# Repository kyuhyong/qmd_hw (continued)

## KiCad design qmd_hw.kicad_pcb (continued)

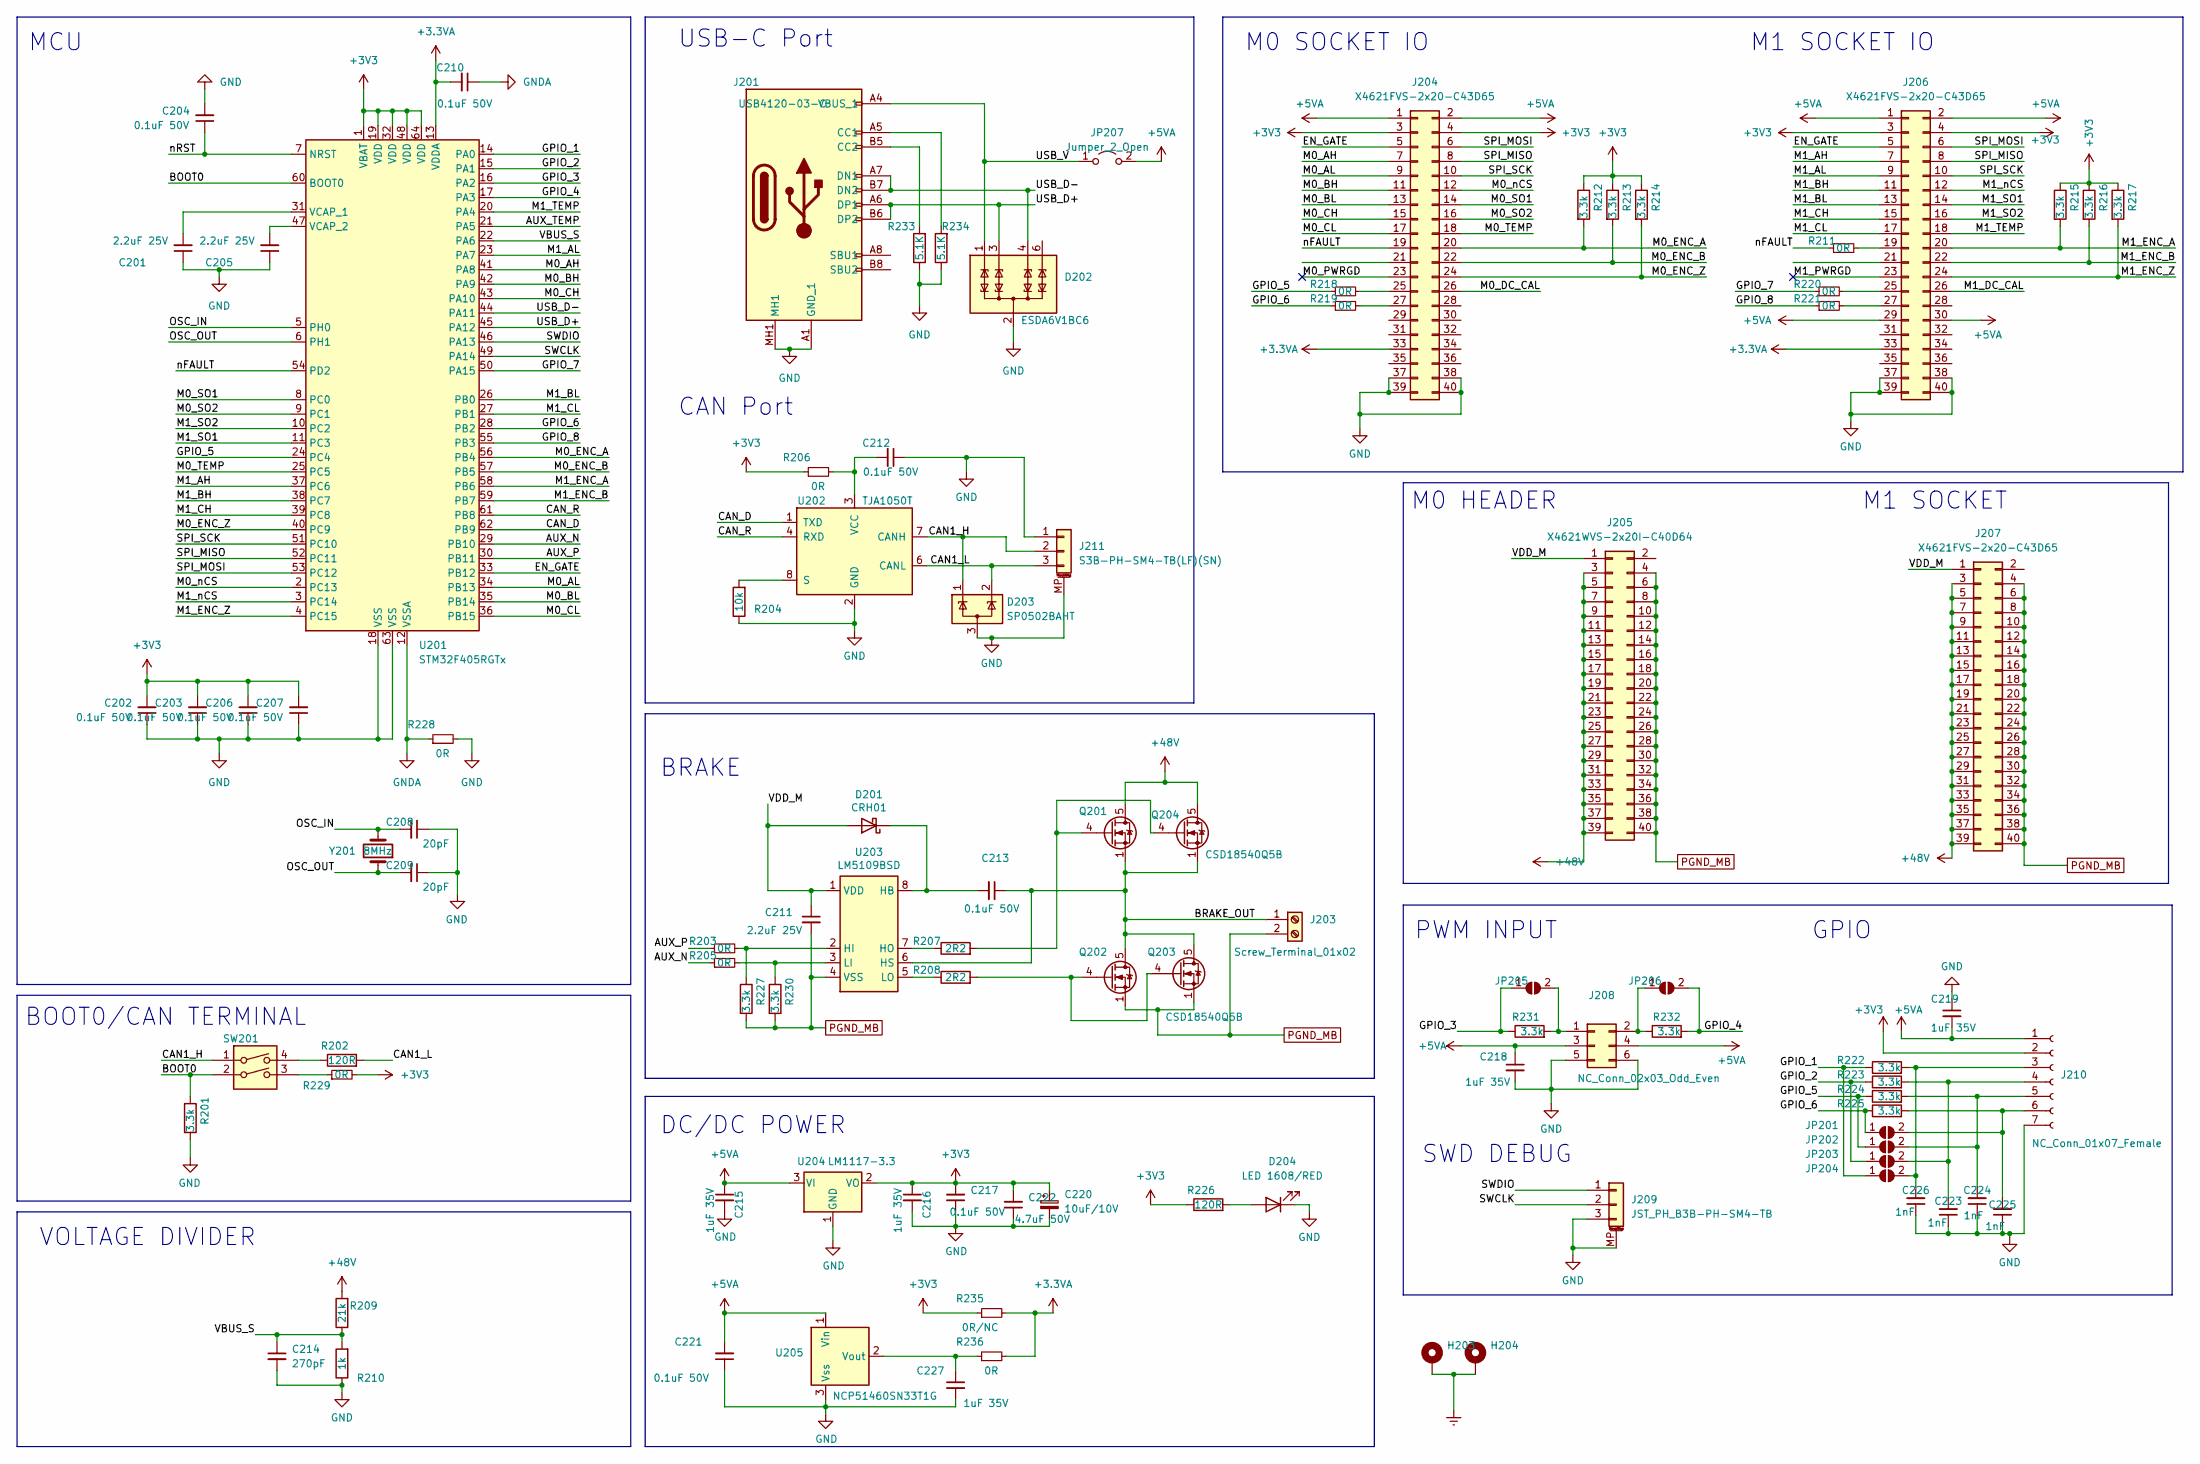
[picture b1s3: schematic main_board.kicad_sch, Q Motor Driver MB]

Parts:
C201, C205, C211: 2.2uF 25V; C_0603_1608Metric; MPN CL10A225KB8NNNC; JLCPN C913904
C202, C203, C204, C206, C207, C210, C212, C213, C217, C221: 0.1uF 50V; C_0603_1608Metric; MPN CL10B104KB8NNNC; JLCPN C1591
C208, C209: 20pF; C_0603_1608Metric; MPN CC0402JRNPO9BN200; JLCPN C107000
C214: 270pF; C_0603_1608Metric; MPN CGA2B2C0G1H271JT0Y0F; JLCPN C695156
C215, C216, C218, C219: 1uF 35V; C_0603_1608Metric; MPN CL05A105KL5NRNC; JLCPN C307413
C220: 10uF/10V; CP_EIA-3216-18_Kemet-A; MPN CA45-A010M106T; JLCPN C127946
C222: 4.7uF 50V; C_0805_2012Metric; MPN GRM219R6YA475KA73D; JLCPN C913498
C223, C224, C225, C226: 1nF; C_0603_1608Metric; MPN CL05B102KB5NNNC; JLCPN C14442
C227: 1uF 35V; C_0603_1608Metric; MPN CGA3E1X7R1V105KT000N; JLCPN C342956
D201: CRH01; SODFL3516X108N; MPN CRH01(TE85L,Q); JLCPN C845528
D202: ESDA6V1BC6; SOT-23-6
D203: SP0502BAHT; SOT-23
D204: LED 1608/RED; LED_0603_1608Metric
H203, H204: MountingHole_Pad; MountingHole_3.2mm_M3_ISO7380_Pad_TopBottom
J201: USB4120-03-C; USB412003C; Mouser Part Number 640-USB4120-03-C
J203: Screw_Terminal_01x02; TB01050802BE
J204, J206, J207: X4621FVS-2x20-C43D65; PinSocket_2x20_P2.00mm_Vertical_SMD; MPN X4621FVS-2x20-C43D65; JLCPN C2883206
J205: X4621WVS-2x20I-C40D64; PinHeader_2x20_P2.0mm_Vertical_SMD_877594051; MPN X4621WVS-2x20I-C40D64; JLCPN C2883178
J208: NC_Conn_02x03_Odd_Even; PinHeader_2x03_P2.54mm_Vertical
J209: JST_PH_B3B-PH-SM4-TB; JST_PH_B3B-PH-SM4-TB_1x03-1MP_P2.00mm_Vertical; JLCPN C160353
J210: NC_Conn_01x07_Female; PinHeader_1x07_P2.54mm_Vertical
J211: S3B-PH-SM4-TB(LF)(SN); JST_S3B-PH-SM4-TB; JLCPN C265101
JP201, JP202, JP203, JP204, JP205, JP206: SolderJumper_2_Open; SolderJumper-2_P1.3mm_Open_RoundedPad1.0x1.5mm
JP207: Jumper_2_Open; SolderJumper-2_P1.3mm_Open_TrianglePad1.0x1.5mm
Q201, Q202, Q203, Q204: CSD18540Q5B; TDSON-8-1; MPN CSD18540Q5BT
R201, R212, R213, R214, R215, R216, R217, R222, R223, R224, R225, R227, R230, R231, R232: 3.3k; R_0603_1608Metric; MPN RC0603JR-073K3L; JLCPN C114432
R202, R226: 120R; R_0603_1608Metric; MPN ERJ-2RKF1200X
R203, R205, R206, R211, R218, R219, R220, R221, R228, R229, R236: 0R; R_0603_1608Metric; MPN RC0603JR-070RL; JLCPN C95177
R204: 10k; R_0603_1608Metric; MPN RC0603FR-0710KL
R207, R208: 2R2; R_0603_1608Metric; MPN RC0603FR-072R2L; JLCPN C112307
R209: 21k; R_0603_1608Metric; JLCPN C112307
R210: 1k; R_0603_1608Metric; MPN RT0603BRE071KL; JLCPN C513397
R233, R234: 5.1K; R_0603_1608Metric; MPN RC0402FR-075K1L
R235: 0R/NC; R_0603_1608Metric; MPN RC0603JR-070RL; JLCPN C95177
SW201: SW_DIP_x02; SW-SMD-4P; MPN 219-2MSTR; JLCPN C2961978
U201: STM32F405RGTx; LQFP-64_10x10mm_P0.5mm
U202: TJA1050T; SOIC-8_3.9x4.9mm_P1.27mm
U203: LM5109BSD; WSON-8-1EP_4x4mm_P0.8mm_EP2.6x3mm_ThermalVias; MPN LM5109BSDX/NOPB
U204: LM1117-3.3; SOT-223
U205: NCP51460SN33T1G; SOT-23; MPN NCP51460SN33T1G; JLCPN C233715
Y201: 8MHz; Crystal_SMD_5032-2Pin_5.0x3.2mm; MPN X50328MSB2GI; JLCPN C115962

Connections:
+3.3VA: C210.2, J204.33, J206.33, R235.2, R236.2, U201.13 (VDDA)
+3V3: C202.2, C203.2, C206.2, C207.2, C216.1, C217.2, C220.1, C222.2, J204.3, J204.4, J206.3, J206.4, J210.2, R206.1, R212.1, R213.1, R214.1, R215.1, R216.1, R217.1, R226.1, R229.2, R235.1, U201.1 (VBAT), U201.19 (VDD), U201.32 (VDD), U201.48 (VDD), U201.64 (VDD), U204.2 (VO), U204.4 (VO)
+5VA: C215.1, C218.1, C219.2, C221.2, J204.1, J204.2, J206.1, J206.2, J206.29, J206.30, J208.3, J208.4, J210.1, JP207.2 (B), U204.3 (VI), U205.1 (Vin)
+48V: J205.3, J205.5, J205.7, J205.9, J205.11, J205.13, J205.15, J205.17, J205.19, J205.21, J205.23, J205.25, J205.27, J205.29, J205.31, J205.33, J205.35, J205.37, J205.39, J207.3, J207.5, J207.7, J207.9, J207.11, J207.13, J207.15, J207.17, J207.19, J207.21, J207.23, J207.25, J207.27, J207.29, J207.31, J207.33, J207.35, J207.37, J207.39, Q201.5 (D), Q204.5 (D), R209.2
/main_board/AUX_N: R205.1, U201.29 (PB10)
/main_board/AUX_P: R203.1, U201.30 (PB11)
/main_board/AUX_TEMP: U201.21 (PA5)
/main_board/BOOT0: R201.1, SW201.2, U201.60 (BOOT0)
/main_board/BRAKE_OUT: C213.1, J203.1, Q201.1 (S), Q201.2 (S), Q201.3 (S), Q202.5 (D), Q203.5 (D), Q204.1 (S), Q204.2 (S), Q204.3 (S), U203.6 (HS)
/main_board/CAN1_H: D203.1 (K), J211.2, SW201.1, U202.7 (CANH)
/main_board/CAN1_L: D203.2 (K), J211.3, R202.2, U202.6 (CANL)
/main_board/CAN_D: U201.62 (PB9), U202.1 (TXD)
/main_board/CAN_R: U201.61 (PB8), U202.4 (RXD)
/main_board/EN_GATE: J204.5, J206.5, U201.33 (PB12)
/main_board/GPIO_1: JP204.1 (A), R222.1, U201.14 (PA0)
/main_board/GPIO_2: JP203.1 (A), R223.1, U201.15 (PA1)
/main_board/GPIO_3: JP205.1 (A), R231.1, U201.16 (PA2)
/main_board/GPIO_4: JP206.2 (B), R232.2, U201.17 (PA3)
/main_board/GPIO_5: JP202.1 (A), R218.1, R224.1, U201.24 (PC4)
/main_board/GPIO_6: JP201.1 (A), R219.1, R225.1, U201.28 (PB2)
/main_board/GPIO_7: R220.1, U201.50 (PA15)
/main_board/GPIO_8: R221.1, U201.55 (PB3)
/main_board/M0_AH: J204.7, U201.41 (PA8)
/main_board/M0_AL: J204.9, U201.34 (PB13)
/main_board/M0_BH: J204.11, U201.42 (PA9)
/main_board/M0_BL: J204.13, U201.35 (PB14)
/main_board/M0_CH: J204.15, U201.43 (PA10)
/main_board/M0_CL: J204.17, U201.36 (PB15)
/main_board/M0_DC_CAL: J204.26
/main_board/M0_ENC_A: J204.20, R212.2, U201.56 (PB4)
/main_board/M0_ENC_B: J204.22, R213.2, U201.57 (PB5)
/main_board/M0_ENC_Z: J204.24, R214.2, U201.40 (PC9)
/main_board/M0_PWRGD: J204.23
/main_board/M0_SO1: J204.14, U201.8 (PC0)
/main_board/M0_SO2: J204.16, U201.9 (PC1)
/main_board/M0_TEMP: J204.18, U201.25 (PC5)
/main_board/M0_nCS: J204.12, U201.2 (PC13)
/main_board/M1_AH: J206.7, U201.37 (PC6)
/main_board/M1_AL: J206.9, U201.23 (PA7)
/main_board/M1_BH: J206.11, U201.38 (PC7)
/main_board/M1_BL: J206.13, U201.26 (PB0)
/main_board/M1_CH: J206.15, U201.39 (PC8)
/main_board/M1_CL: J206.17, U201.27 (PB1)
/main_board/M1_DC_CAL: J206.26
/main_board/M1_ENC_A: J206.20, R215.2, U201.58 (PB6)
/main_board/M1_ENC_B: J206.22, R216.2, U201.59 (PB7)
/main_board/M1_ENC_Z: J206.24, R217.2, U201.4 (PC15)
/main_board/M1_PWRGD: J206.23
/main_board/M1_SO1: J206.14, U201.11 (PC3)
/main_board/M1_SO2: J206.16, U201.10 (PC2)
/main_board/M1_TEMP: J206.18, U201.20 (PA4)
/main_board/M1_nCS: J206.12, U201.3 (PC14)
/main_board/OSC_IN: C208.2, U201.5 (PH0), Y201.2
/main_board/OSC_OUT: C209.2, U201.6 (PH1), Y201.1
/main_board/SPI_MISO: J204.8, J206.8, U201.52 (PC11)
/main_board/SPI_MOSI: J204.6, J206.6, U201.53 (PC12)
/main_board/SPI_SCK: J204.10, J206.10, U201.51 (PC10)
/main_board/SWCLK: J209.2, U201.49 (PA14)
/main_board/SWDIO: J209.1, U201.46 (PA13)
/main_board/USB_D+: D202.3 (TVS2), J201.A6 (DP1), J201.B6 (DP2), U201.45 (PA12)
/main_board/USB_D-: D202.4 (TVS3), J201.A7 (DN1), J201.B7 (DN2), U201.44 (PA11)
/main_board/USB_V: D202.1 (TVS1), J201.A4 (VBUS_1), J201.A9 (VBUS_2), J201.B4 (VBUS_3), J201.B9 (VBUS_4), JP207.1 (A)
/main_board/VBUS_S: C214.1, R209.1, R210.2, U201.22 (PA6)
/main_board/VDD_M: C211.1, D201.2 (A), J205.1, J207.1, U203.1 (VDD)
/main_board/nFAULT: J204.19, R211.1, U201.54 (PD2)
/main_board/nRST: C204.1, U201.7 (NRST)
Earth: H203.1, H204.1
GND: C201.1, C202.1, C203.1, C204.2, C205.1, C206.1, C207.1, C208.1, C209.1, C212.1, C214.2, C215.2, C216.2, C217.1, C218.2, C219.1, C220.2, C221.1, C222.1, C223.1, C224.1, C225.1, C226.1, C227.2, D202.2 (COM), D202.5 (COM), D203.3 (A), D204.1 (K), J201.A1 (GND_1), J201.A12 (GND_2), J201.B1 (GND_3), J201.B12 (GND_4), J201.MH1, J201.MH2, J201.MH3, J201.MH4, J204.37, J204.38, J204.39, J204.40, J206.37, J206.38, J206.39, J206.40, J208.5, J208.6, J209.3, J209.MP (MountPin), J210.7, J211.1, J211.MP (MountPin), R201.2, R204.1, R210.1, R228.2, R233.1, R234.1, U201.18 (VSS), U201.63 (VSS), U202.2 (GND), U204.1 (GND), U205.3 (Vss)
GNDA: C210.1, R228.1, U201.12 (VSSA)
unnamed: C213.2, D201.1 (K), U203.8 (HB)
unnamed: D204.2 (A), R226.2
unnamed: J201.A5 (CC1), R234.2
unnamed: J201.B5 (CC2), R233.2
unnamed: J204.25, R218.2
unnamed: J204.27, R219.2
unnamed: J206.19, R211.2
unnamed: J206.25, R220.2
unnamed: J206.27, R221.2
unnamed: J208.1, JP205.2 (B), R231.2
unnamed: J208.2, JP206.1 (A), R232.1
unnamed: C226.2, J210.3, JP204.2 (B), R222.2
unnamed: C223.2, J210.4, JP203.2 (B), R223.2
unnamed: C224.2, J210.5, JP202.2 (B), R224.2
unnamed: C225.2, J210.6, JP201.2 (B), R225.2
unnamed: Q201.4 (G), Q204.4 (G), R207.2
unnamed: Q202.4 (G), Q203.4 (G), R208.2
unnamed: R202.1, SW201.4
unnamed: R229.1, SW201.3
unnamed: C201.2, U201.31 (VCAP_1)
unnamed: C205.2, U201.47 (VCAP_2)
unnamed: R204.2, U202.8 (S)
unnamed: C212.2, R206.2, U202.3 (VCC)
unnamed: R203.2, R227.1, U203.2 (HI)
unnamed: R207.1, U203.7 (HO)
unnamed: R205.2, R230.1, U203.3 (LI)
unnamed: R208.1, U203.5 (LO)
unnamed: C227.1, R236.1, U205.2 (Vout)
PGND_MB: C211.2, J203.2, J205.4, J205.6, J205.8, J205.10, J205.12, J205.14, J205.16, J205.18, J205.20, J205.22, J205.24, J205.26, J205.28, J205.30, J205.32, J205.34, J205.36, J205.38, J205.40, J207.4, J207.6, J207.8, J207.10, J207.12, J207.14, J207.16, J207.18, J207.20, J207.22, J207.24, J207.26, J207.28, J207.30, J207.32, J207.34, J207.36, J207.38, J207.40, Q202.1 (S), Q202.2 (S), Q202.3 (S), Q203.1 (S), Q203.2 (S), Q203.3 (S), R227.2, R230.2, U203.4 (VSS), U203.9 (VSS)

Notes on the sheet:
DC/DC POWER
GPIO
MCU
PWM INPUT
BRAKE
M0 SOCKET IO
SWD DEBUG
M1 SOCKET
USB-C Port
M1 SOCKET IO
VOLTAGE DIVIDER
BOOT0/CAN TERMINAL
M0 HEADER
CAN Port

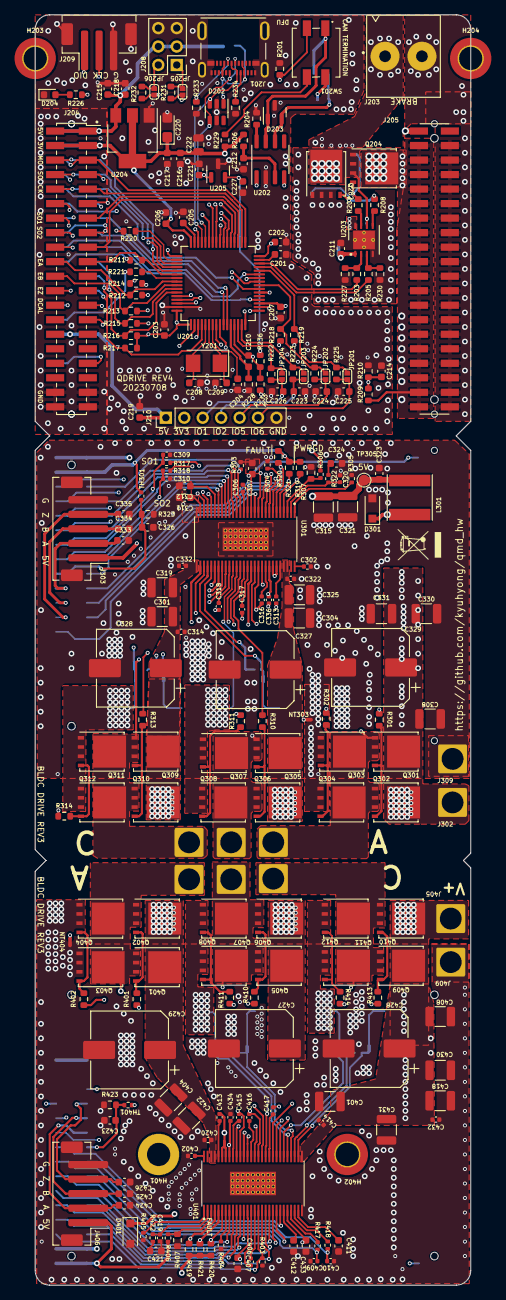
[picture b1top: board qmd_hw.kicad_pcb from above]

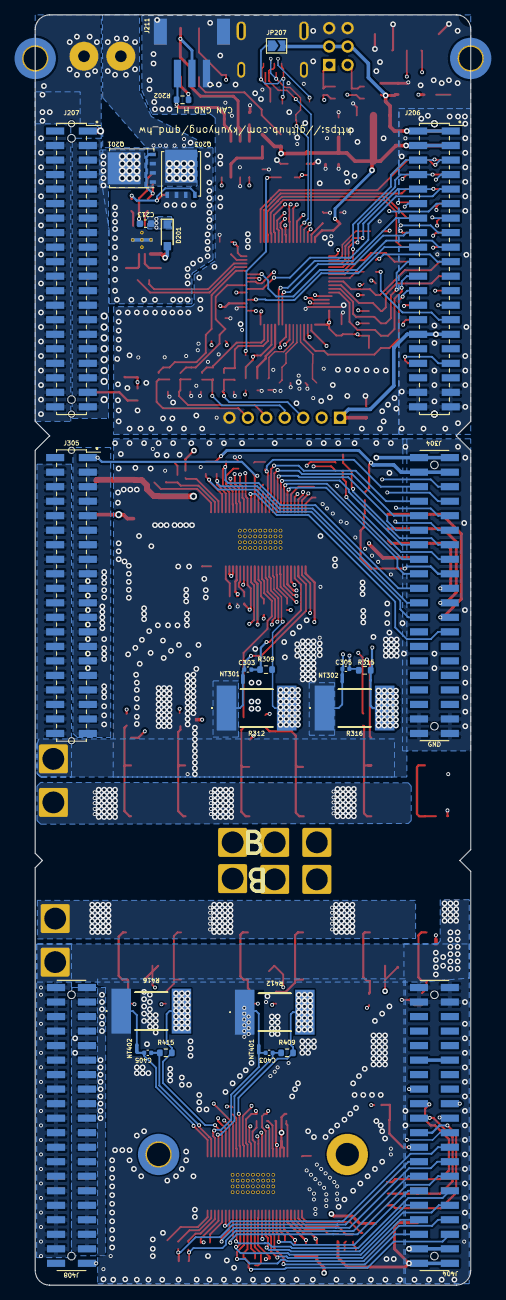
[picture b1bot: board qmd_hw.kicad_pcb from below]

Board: 4 copper layers, 60.0 x 175.0 mm, 267 parts (29 on the bottom side), 224 nets.

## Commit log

2023-05-19 Update artwork for M0 board
2023-05-20 Added layer 3
2023-05-21 Updated route per BOOSTXL reference design
2023-05-23 Re-route
2023-06-25 Fixed bugs and parts update
2023-07-09 Updated MB
2023-07-10 Few updates
